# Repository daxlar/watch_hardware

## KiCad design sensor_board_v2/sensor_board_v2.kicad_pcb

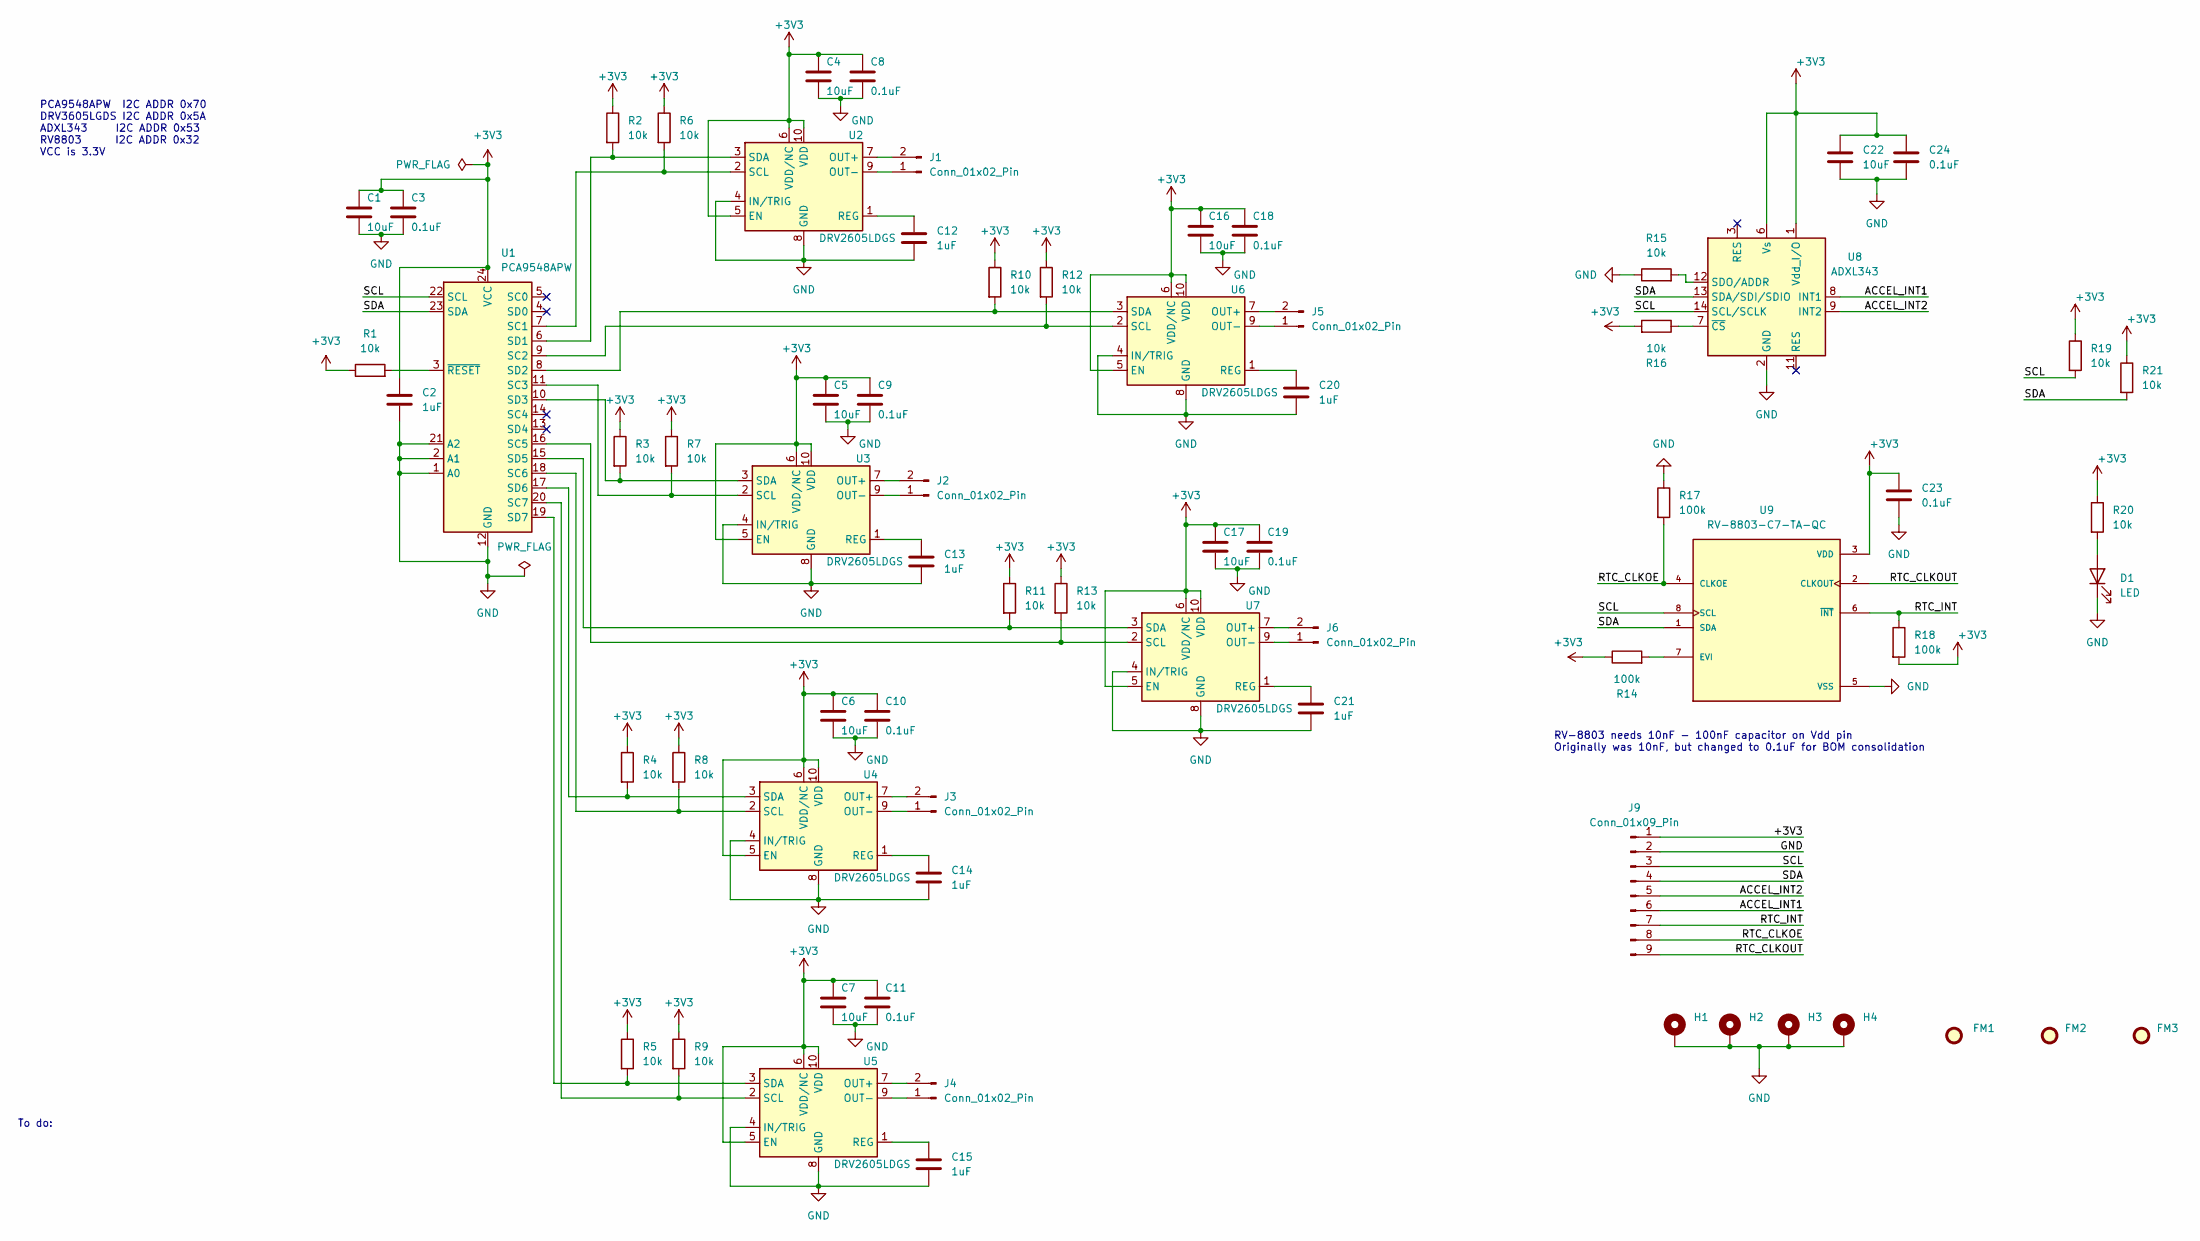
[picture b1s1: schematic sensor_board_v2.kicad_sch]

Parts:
C1, C4, C5, C6, C7, C16, C17, C22: 10uF; C_0603_1608Metric; Manufacturer Part Number GRM188C80J106MEA6D; LCSC C576469
C2, C12, C13, C14, C15, C20, C21: 1uF; C_0603_1608Metric; Manufacturer Part Number C0603C105K4PAC7867; LCSC C561801
C3, C8, C9, C10, C11, C18, C19, C24: 0.1uF; C_0402_1005Metric; Manufacturer Part Number CGA2B2X5R1A104K050BA; LCSC C3847691
C23: 0.1uF; C_0402_1005Metric; Manufacturer Part Number GRM155R71C103JA01D; LCSC C88947
D1: LED; LED_0402_1005Metric; Manufacturer Part Number SML-P11UTT86R; LCSC C510300
FM1, FM2, FM3: Fiducial; Fiducial_1mm_Mask2mm
H1, H2, H3, H4: MountingHole_Pad; MountingHole_2.2mm_M2_Pad
J1, J2, J3, J4, J5, J6: Conn_01x02_Pin; PinHeader_1x02_P2.54mm_Vertical
J9: Conn_01x09_Pin; PinHeader_1x09_P2.54mm_Vertical
R1, R2, R3, R4, R5, R6, R7, R8, R9, R10, R11, R12, R13, R15, R16, R19, R20, R21: 10k; R_0402_1005Metric; Manufacturer Part Number RC0402FR-0710KL; LCSC C60490
R14, R17, R18: 100k; R_0402_1005Metric; Manufacturer Part Number RC0402FR-07100KL; LCSC C60491
U1: PCA9548APW; TSSOP-24_4.4x7.8mm_P0.65mm; Manufacturer Part Number PCA9548APW,118; LCSC C21198
U2, U3, U4, U5, U6, U7: DRV2605LDGS; VSSOP-10_3x3mm_P0.5mm; Manufacturer Part Number DRV2605LDGSR; LCSC C527464
U8: ADXL343; LGA-14_3x5mm_P0.8mm_LayoutBorder1x6y; Manufacturer Part Number ADXL343BCCZ-RL7; LCSC C579454
U9: RV-8803-C7-TA-QC; IC_RV-8803-C7-TA-QC; PARTREV 5.1/06.2018; LCSC C2846926

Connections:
+3V3: C1.1, C2.1, C3.1, C4.1, C5.1, C6.1, C7.1, C8.1, C9.1, C10.1, C11.1, C16.1, C17.1, C18.1, C19.1, C22.1, C23.1, C24.1, J9.1, R1.1, R2.1, R3.1, R4.1, R5.1, R6.1, R7.1, R8.1, R9.1, R10.1, R11.1, R12.1, R13.1, R14.1, R16.2, R18.2, R19.1, R20.1, R21.1, U1.24 (VCC), U2.5 (EN), U2.6 (VDD/NC), U2.10 (VDD), U3.5 (EN), U3.6 (VDD/NC), U3.10 (VDD), U4.5 (EN), U4.6 (VDD/NC), U4.10 (VDD), U5.5 (EN), U5.6 (VDD/NC), U5.10 (VDD), U6.5 (EN), U6.6 (VDD/NC), U6.10 (VDD), U7.5 (EN), U7.6 (VDD/NC), U7.10 (VDD), U8.1 (Vdd_I/O), U8.6 (Vs), U9.3 (VDD)
/ACCEL_INT1: J9.6, U8.8 (INT1)
/ACCEL_INT2: J9.5, U8.9 (INT2)
/RTC_CLKOE: J9.8, R17.2, U9.4 (CLKOE)
/RTC_CLKOUT: J9.9, U9.2 (CLKOUT)
/RTC_INT: J9.7, R18.1, U9.6 (~INT)
/SCL: J9.3, R19.2, U1.22 (SCL), U8.14 (SCL/SCLK), U9.8 (SCL)
/SDA: J9.4, R21.2, U1.23 (SDA), U8.13 (SDA/SDI/SDIO), U9.1 (SDA)
GND: C1.2, C2.2, C3.2, C4.2, C5.2, C6.2, C7.2, C8.2, C9.2, C10.2, C11.2, C12.2, C13.2, C14.2, C15.2, C16.2, C17.2, C18.2, C19.2, C20.2, C21.2, C22.2, C23.2, C24.2, D1.1 (K), H1.1, H2.1, H3.1, H4.1, J9.2, R15.1, R17.1, U1.1 (A0), U1.2 (A1), U1.12 (GND), U1.21 (A2), U2.4 (IN/TRIG), U2.8 (GND), U3.4 (IN/TRIG), U3.8 (GND), U4.4 (IN/TRIG), U4.8 (GND), U5.4 (IN/TRIG), U5.8 (GND), U6.4 (IN/TRIG), U6.8 (GND), U7.4 (IN/TRIG), U7.8 (GND), U8.2 (GND), U8.4 (GND), U8.5 (GND), U9.5 (VSS)
unnamed: D1.2 (A), R20.2
unnamed: J1.1, U2.9 (OUT-)
unnamed: J1.2, U2.7 (OUT+)
unnamed: J2.1, U3.9 (OUT-)
unnamed: J2.2, U3.7 (OUT+)
unnamed: J3.1, U4.9 (OUT-)
unnamed: J3.2, U4.7 (OUT+)
unnamed: J4.1, U5.9 (OUT-)
unnamed: J4.2, U5.7 (OUT+)
unnamed: J5.1, U6.9 (OUT-)
unnamed: J5.2, U6.7 (OUT+)
unnamed: J6.1, U7.9 (OUT-)
unnamed: J6.2, U7.7 (OUT+)
unnamed: R6.2, U1.7 (SC1), U2.2 (SCL)
unnamed: R12.2, U1.9 (SC2), U6.2 (SCL)
unnamed: R7.2, U1.11 (SC3), U3.2 (SCL)
unnamed: R13.2, U1.16 (SC5), U7.2 (SCL)
unnamed: R8.2, U1.18 (SC6), U4.2 (SCL)
unnamed: R9.2, U1.20 (SC7), U5.2 (SCL)
unnamed: R2.2, U1.6 (SD1), U2.3 (SDA)
unnamed: R10.2, U1.8 (SD2), U6.3 (SDA)
unnamed: R3.2, U1.10 (SD3), U3.3 (SDA)
unnamed: R11.2, U1.15 (SD5), U7.3 (SDA)
unnamed: R4.2, U1.17 (SD6), U4.3 (SDA)
unnamed: R5.2, U1.19 (SD7), U5.3 (SDA)
unnamed: R1.2, U1.3 (~RESET)
unnamed: C12.1, U2.1 (REG)
unnamed: C13.1, U3.1 (REG)
unnamed: C14.1, U4.1 (REG)
unnamed: C15.1, U5.1 (REG)
unnamed: C20.1, U6.1 (REG)
unnamed: C21.1, U7.1 (REG)
unnamed: R15.2, U8.12 (SDO/ADDR)
unnamed: R16.1, U8.7 (~CS)
unnamed: R14.2, U9.7 (EVI)

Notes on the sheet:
To do:
RV-8803 needs 10nF - 100nF capacitor on Vdd pin Originally was 10nF, but changed to 0.1uF for BOM consolidation
PCA9548APW I2C ADDR 0x70 DRV3605LGDS I2C ADDR 0x5A ADXL343 I2C ADDR 0x53 RV8803 I2C ADDR 0x32 VCC is 3.3V

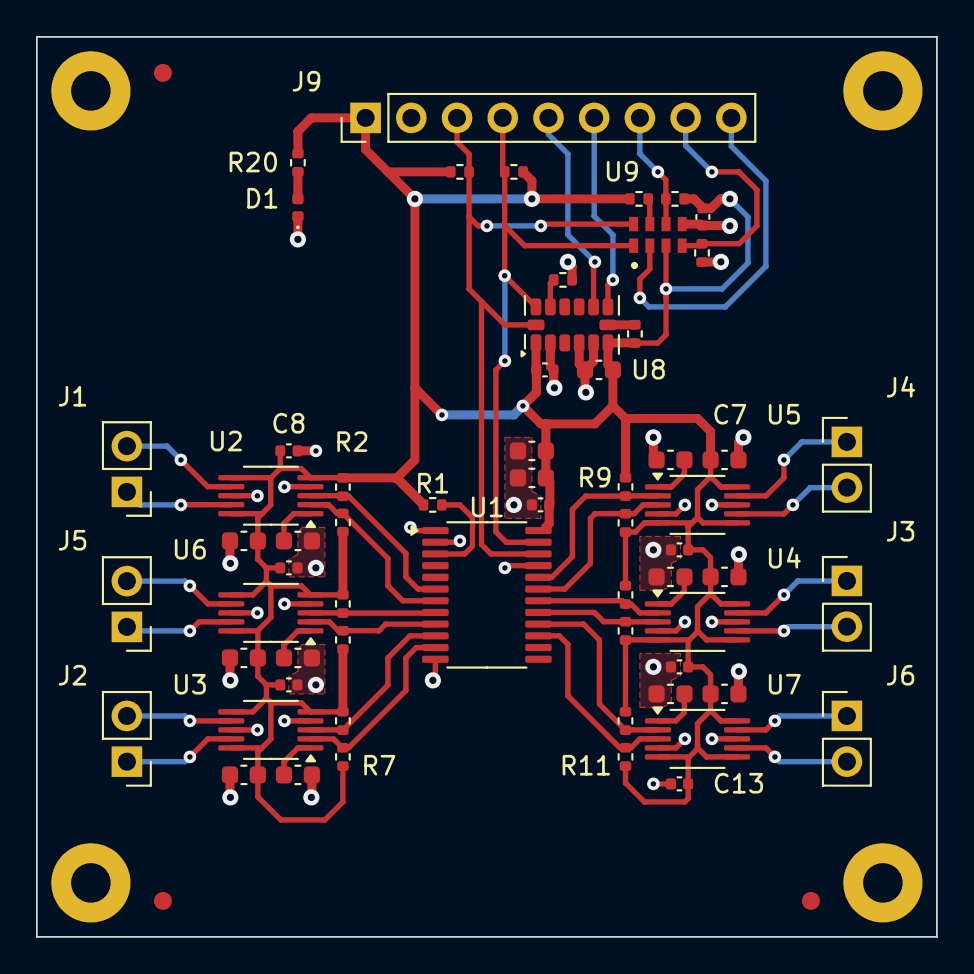
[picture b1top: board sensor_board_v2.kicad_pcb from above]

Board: 4 copper layers, 50.0 x 50.0 mm, 69 parts (0 on the bottom side), 44 nets.

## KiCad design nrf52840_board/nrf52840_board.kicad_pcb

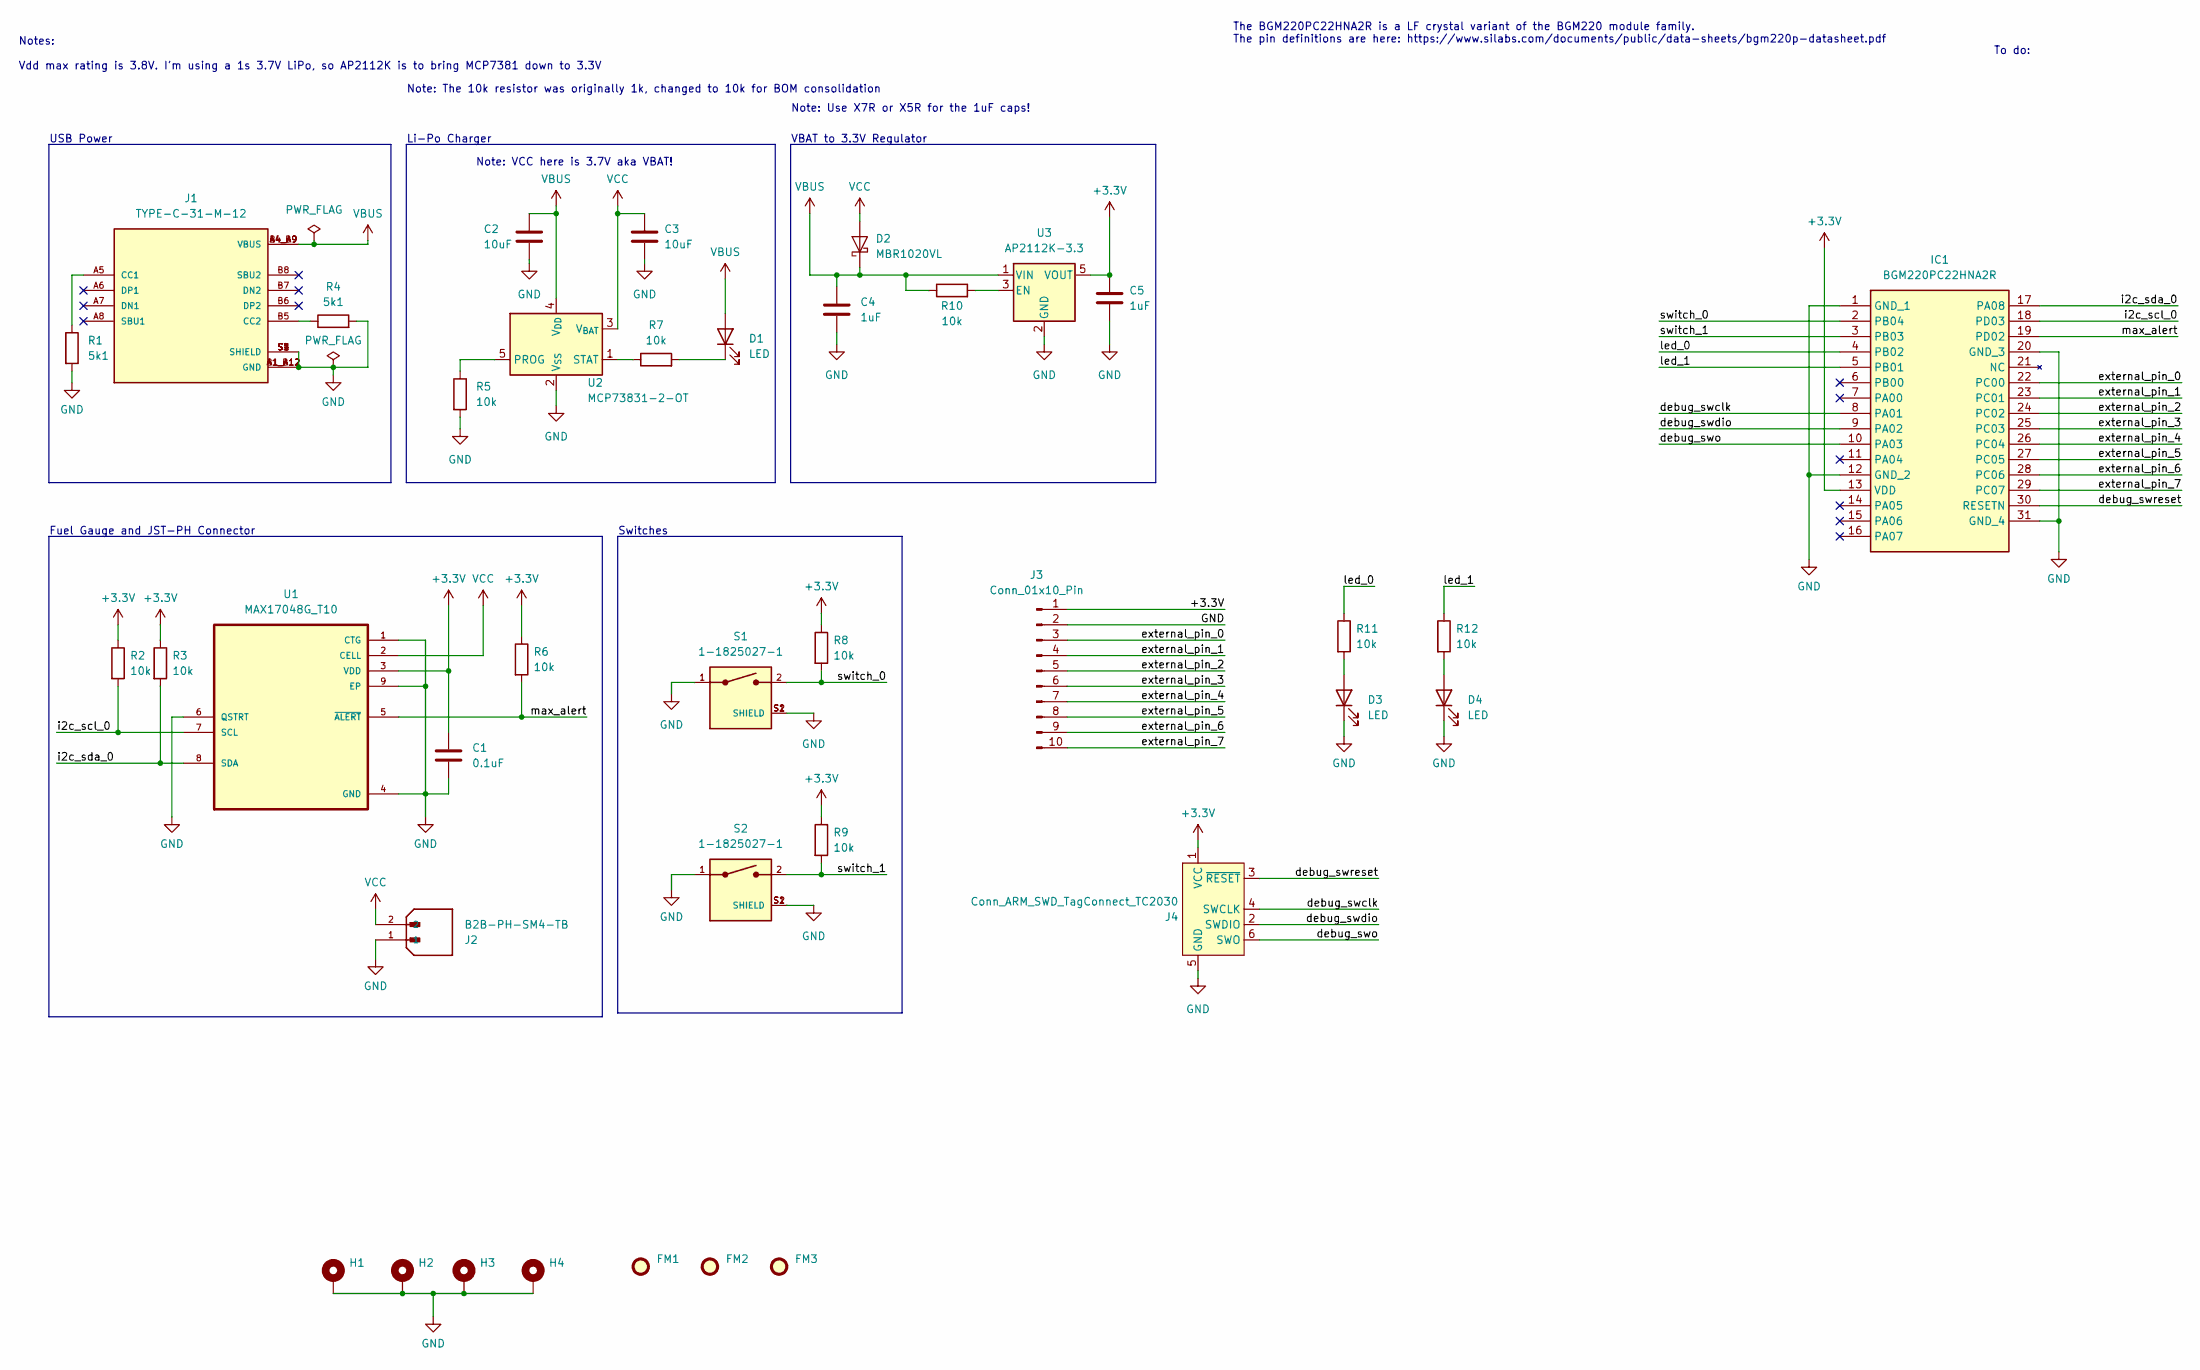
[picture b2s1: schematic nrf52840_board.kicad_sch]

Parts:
C1: 0.1uF; C_0402_1005Metric
C2, C3: 10uF; C_0603_1608Metric
C4, C5: 1uF; C_0603_1608Metric
D1, D3, D4: LED; LED_0402_1005Metric
D2: MBR1020VL; D_SOD-123F
FM1, FM2, FM3: Fiducial; Fiducial_1mm_Mask2mm
H1, H2, H3, H4: MountingHole_Pad; MountingHole_2.2mm_M2_Pad
IC1: BGM220PC22HNA2R; Manufacturer_Part_Number BGM220PC22HNA2R
J1: TYPE-C-31-M-12; HRO_TYPE-C-31-M-12; PARTREV 2020.12.08
J2: B2B-PH-SM4-TB; JST_B2B-PH-SM4-TB; PARTREV N/A
J3: Conn_01x10_Pin; PinHeader_1x10_P2.54mm_Vertical
J4: Conn_ARM_SWD_TagConnect_TC2030; Tag-Connect_TC2030-IDC-FP_2x03_P1.27mm_Vertical
R1, R4: 5k1; R_0402_1005Metric
R2, R3, R5, R6, R7, R8, R9, R10, R11, R12: 10k; R_0402_1005Metric
S1, S2: 1-1825027-1; SW_1-1825027-1; PARTREV G4
U1: MAX17048G_T10; SON50P200X200X80-9N
U2: MCP73831-2-OT; SOT-23-5
U3: AP2112K-3.3; SOT-23-5

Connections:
+3.3V: C1.1, C5.1, IC1.13 (VDD), J3.1, J4.1 (VCC), R2.1, R3.1, R6.1, R8.1, R9.1, U1.3 (VDD), U3.5 (VOUT)
/debug_swclk: IC1.8 (PA01), J4.4 (SWCLK)
/debug_swdio: IC1.9 (PA02), J4.2 (SWDIO)
/debug_swo: IC1.10 (PA03), J4.6 (SWO)
/debug_swreset: IC1.30 (RESETN), J4.3 (~RESET)
/external_pin_0: IC1.22 (PC00), J3.3
/external_pin_1: IC1.23 (PC01), J3.4
/external_pin_2: IC1.24 (PC02), J3.5
/external_pin_3: IC1.25 (PC03), J3.6
/external_pin_4: IC1.26 (PC04), J3.7
/external_pin_5: IC1.27 (PC05), J3.8
/external_pin_6: IC1.28 (PC06), J3.9
/external_pin_7: IC1.29 (PC07), J3.10
/i2c_scl_0: IC1.18 (PD03), R2.2, U1.7 (SCL)
/i2c_sda_0: IC1.17 (PA08), R3.2, U1.8 (SDA)
/led_0: IC1.4 (PB02), R11.1
/led_1: IC1.5 (PB01), R12.1
/max_alert: IC1.19 (PD02), R6.2, U1.5 (~ALERT)
/switch_0: IC1.2 (PB04), R8.2, S1.2
/switch_1: IC1.3 (PB03), R9.2, S2.2
GND: C1.2, C2.1, C3.1, C4.2, C5.2, D3.1 (K), D4.1 (K), H1.1, H2.1, H3.1, H4.1, IC1.1 (GND_1), IC1.12 (GND_2), IC1.20 (GND_3), IC1.31 (GND_4), J1.A1_B12 (GND), J1.B1_A12 (GND), J1.S1 (SHIELD), J1.S2 (SHIELD), J1.S3 (SHIELD), J1.S4 (SHIELD), J2.1, J3.2, J4.5 (GND), R1.2, R4.2, R5.2, S1.1, S1.S1 (SHIELD), S1.S2 (SHIELD), S2.1, S2.S1 (SHIELD), S2.S2 (SHIELD), U1.1 (CTG), U1.4 (GND), U1.6 (QSTRT), U1.9 (EP), U2.2 (V_{SS}), U3.2 (GND)
unnamed: D1.1 (K), R7.2
unnamed: D3.2 (A), R11.2
unnamed: D4.2 (A), R12.2
unnamed: J1.A5 (CC1), R1.1
unnamed: J1.B5 (CC2), R4.1
unnamed: R5.1, U2.5 (PROG)
unnamed: R7.1, U2.1 (STAT)
unnamed: R10.2, U3.3 (EN)
VBUS: C2.2, C4.1, D1.2 (A), D2.1 (K), J1.A4_B9 (VBUS), J1.B4_A9 (VBUS), R10.1, U2.4 (V_{DD}), U3.1 (VIN)
VCC: C3.2, D2.2 (A), J2.2, U1.2 (CELL), U2.3 (V_{BAT})

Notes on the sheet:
Li-Po Charger
Note: The 10k resistor was originally 1k, changed to 10k for BOM consolidation
VBAT to 3.3V Regulator
USB Power
Switches
Fuel Gauge and JST-PH Connector
To do:
Note: VCC here is 3.7V aka VBAT!
The BGM220PC22HNA2R is a LF crystal variant of the BGM220 module family. The pin definitions are here: https://www.silabs.com/documents/public/data-sheets/bgm220p-datasheet.pdf
Notes: Vdd max rating is 3.8V. I'm using a 1s 3.7V LiPo, so AP2112K is to bring MCP7381 down to 3.3V
Note: Use X7R or X5R for the 1uF caps!

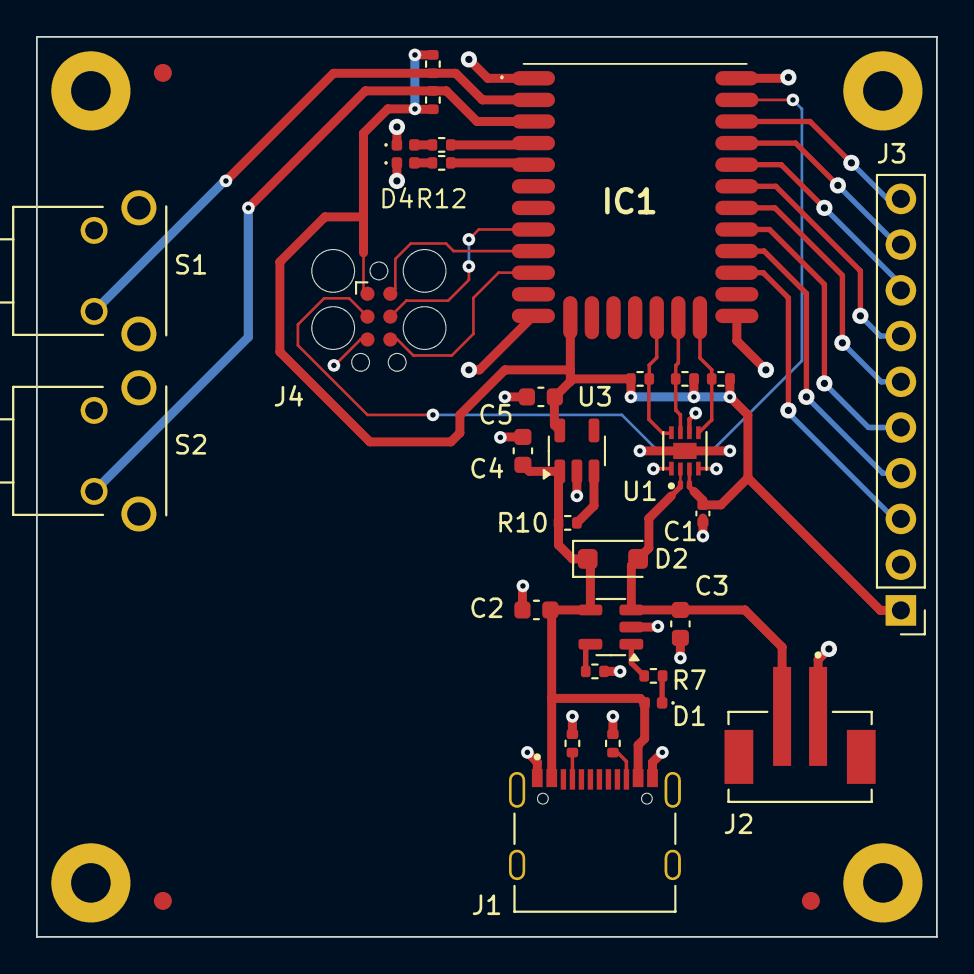
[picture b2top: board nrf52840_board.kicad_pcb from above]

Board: 4 copper layers, 50.0 x 50.0 mm, 38 parts (0 on the bottom side), 31 nets.

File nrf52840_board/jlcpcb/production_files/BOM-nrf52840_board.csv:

Comment,Designator,Footprint,LCSC
B2B-PH-SM4-TB,J2,JST_B2B-PH-SM4-TB,C160352
TYPE-C-31-M-12,J1,HRO_TYPE-C-31-M-12,C165948
1-1825027-1,"S1,S2",SW_1-1825027-1,C266183
MAX17048G_T10,U1,SON50P200X200X80-9N,C2682616
10k,"R10,R11,R12,R2,R3,R5,R6,R7,R8,R9",R_0402_1005Metric,C308028
10uF,"C2,C3",C_0603_1608Metric,C3879288
MCP73831-2-OT,U2,SOT-23-5,C424093
AP2112K-3.3,U3,SOT-23-5,C51118
LED,"D1,D3,D4",LED_0402_1005Metric,C5137326
5k1,"R1,R4",R_0402_1005Metric,C5157654
0.1uF,C1,C_0402_1005Metric,

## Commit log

2024-01-03 adding small TODO
2024-01-03 making a directory for the sensor_board
2024-02-16 finished preliminary layout
2024-02-17 added jlcpcb bouni extension, rotated parts and found lcsc part numbers
2024-02-17 fixed bypass and decoupling C for pca9548
2024-02-24 schematics 90% done
2024-02-26 schematics done
2024-03-08 changed processor to efr32bg22, but it's still named nrf52840 because it's hard to change filenames with kicad
2024-03-11 v1 processor board done
2024-03-13 sensor_board v2 is done
